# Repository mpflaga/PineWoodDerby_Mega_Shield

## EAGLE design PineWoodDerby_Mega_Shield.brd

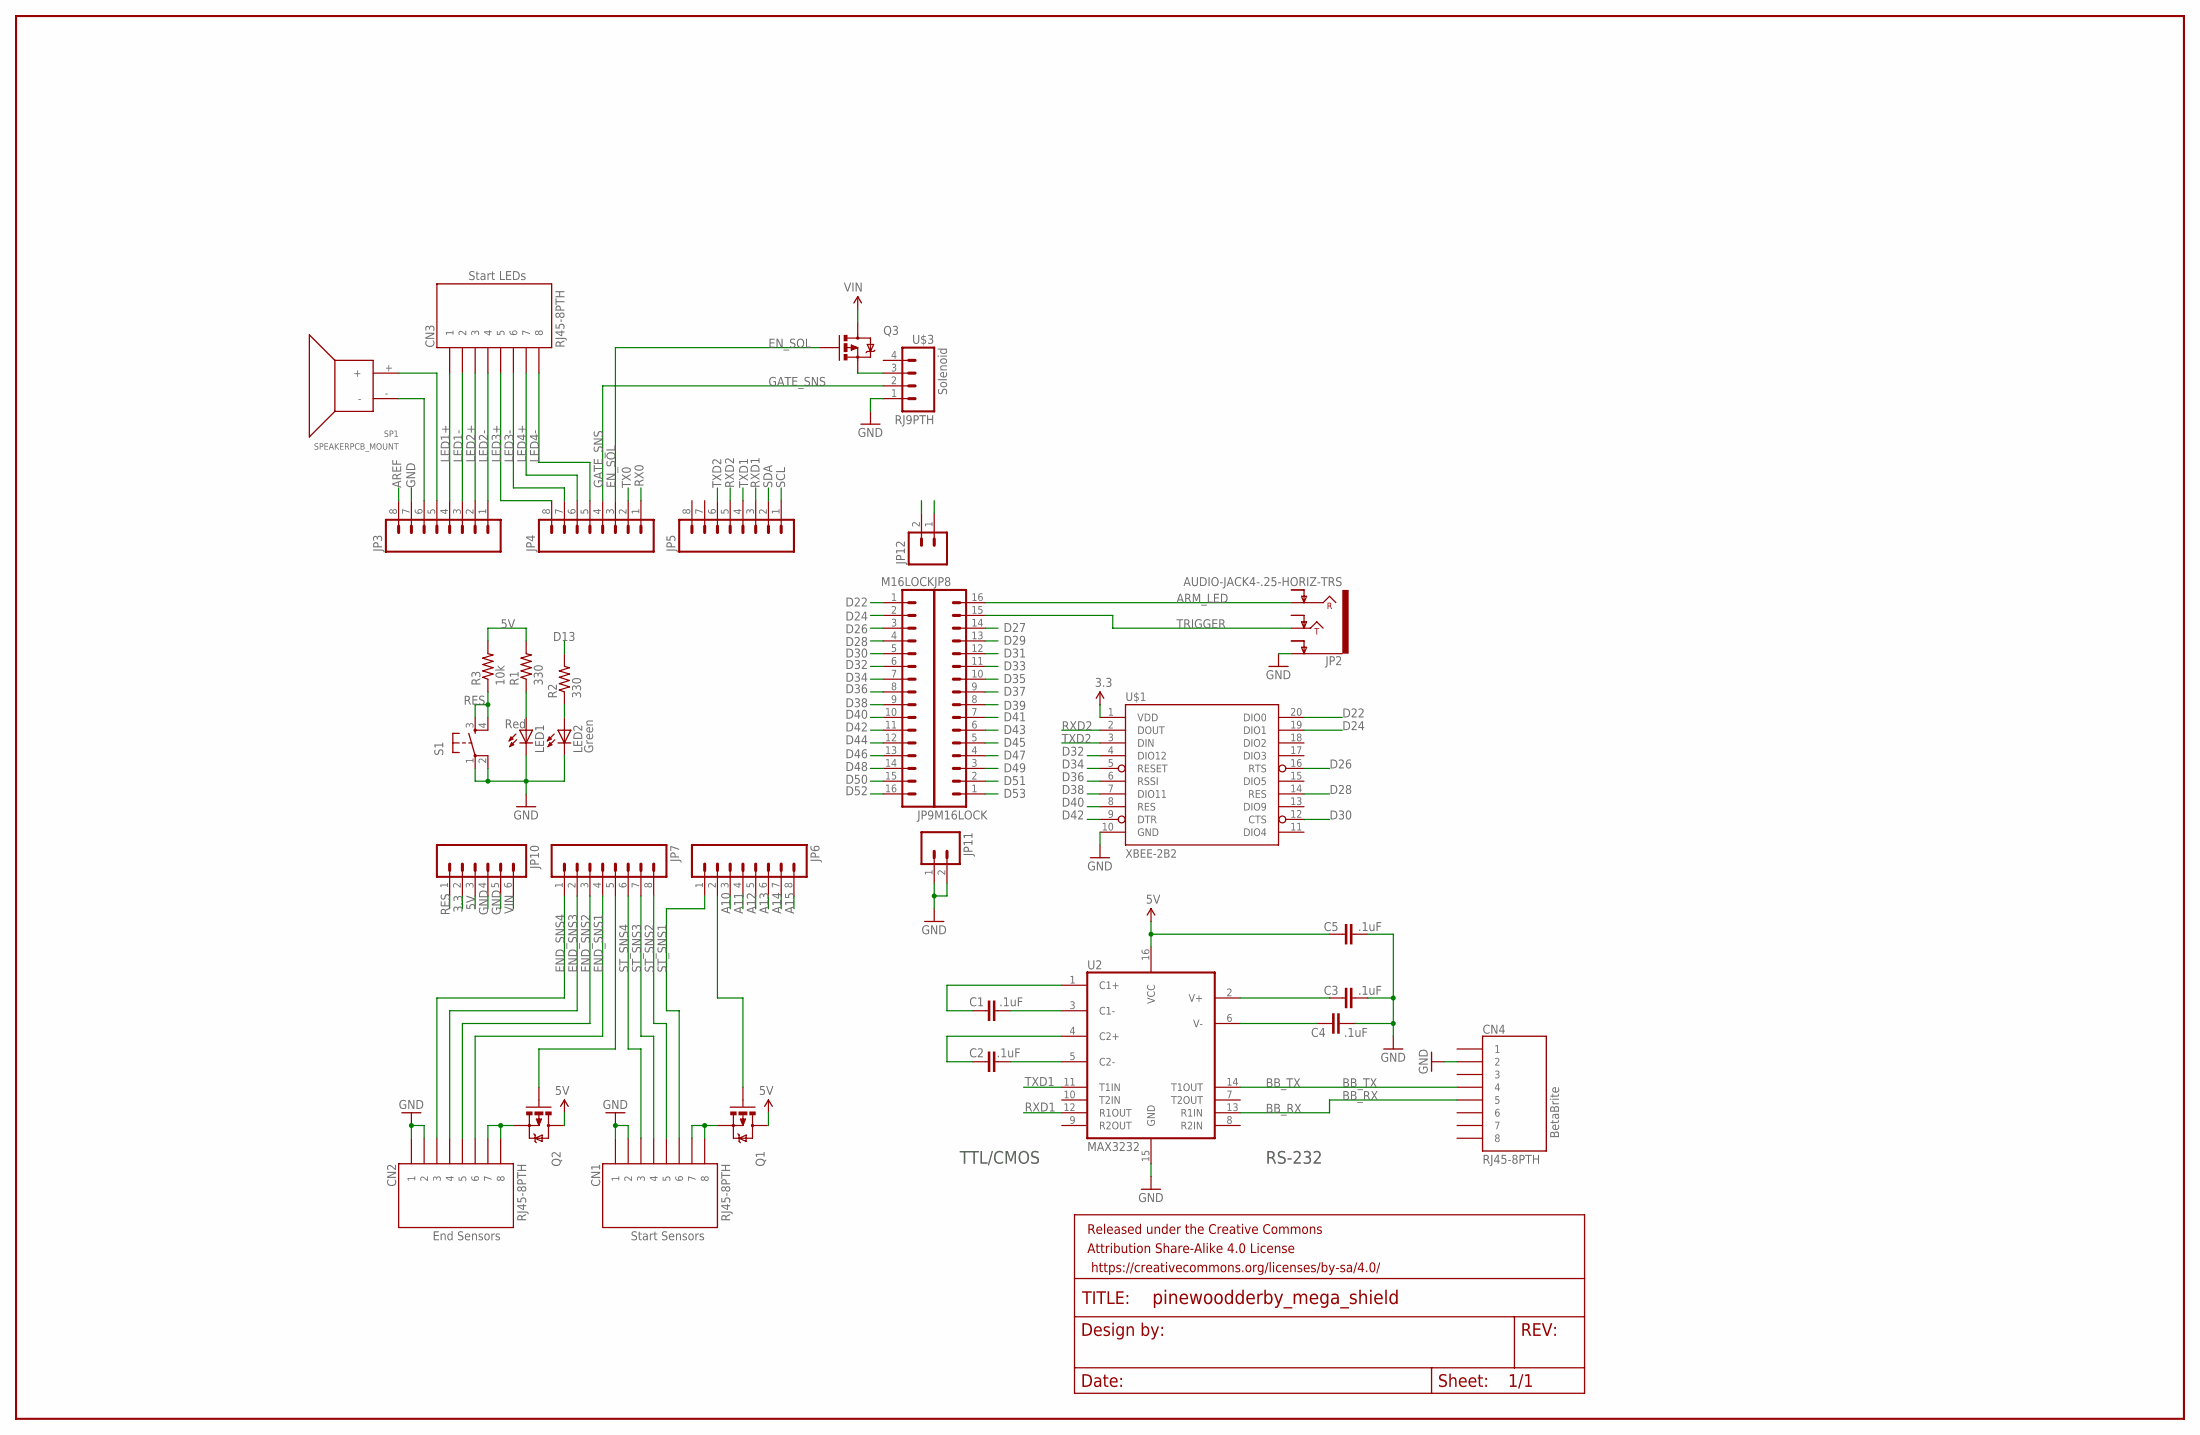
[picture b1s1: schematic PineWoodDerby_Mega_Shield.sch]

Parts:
C1, C2, C3, C4, C5: .1uF; 0402-CAP
CN1, CN2, CN3, CN4: RJ45-8PTH; RJ45-8
FRAME2: FRAME-LEDGER; CREATIVE_COMMONS
JP2: AUDIO-JACK4-.25-HORIZ-TRS; AUDIO-JACK-.25-INCH-HORIZ-PTH
JP3, JP4, JP5, JP6, JP7: M08LOCK; 1X08_LOCK
JP8, JP9: M16LOCK; 1X16_LOCK
JP10: M06LOCK; 1X06_LOCK
JP11, JP12: M02LOCK; 1X02_LOCK
LED1: Red; LED5MM
LED2: Green; LED5MM
Q1, Q2, Q3: MOSFET-PCHANNELFQP27P06; TO220V
R1, R2: 330; AXIAL-0.3
R3: 10k; AXIAL-0.3
S1: TAC_SWITCHPTH; TACTILE-PTH
SP1: SPEAKERPCB_MOUNT; PCB_MOUNT_SPEAKER
U2: MAX3232; SO016
U$1: XBEE-2B2; XBEE-SILK
U$3: RJ9PTH; RJ9

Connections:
3.3: JP10.2, U$1.1 (VDD)
5V: C5.1, JP10.3, Q1.2 (D), Q2.2 (D), R1.P$2 (2), R3.P$2 (2), U2.16 (VCC)
5V@1: JP12.1, JP12.2
A10: JP6.3
A11: JP6.4
A12: JP6.5
A13: JP6.6
A14: JP6.7
A15: JP6.8
AREF: JP3.8
ARM_LED: JP2.RING, JP8.16
BB_RX: CN4.5, U2.13 (R1IN)
BB_TX: CN4.4, U2.14 (T1OUT)
C1+: C1.1, U2.1 (C1+)
C1-: C1.2, U2.3 (C1-)
C2+: C2.1, U2.4 (C2+)
C2-: C2.2, U2.5 (C2-)
D13: R2.P$2 (2)
D22: JP9.1, U$1.20 (DIO0)
D24: JP9.2, U$1.19 (DIO1)
D26: JP9.3, U$1.16 (RTS)
D27: JP8.14
D28: JP9.4, U$1.14 (RES)
D29: JP8.13
D30: JP9.5, U$1.12 (CTS)
D31: JP8.12
D32: JP9.6, U$1.4 (DIO12)
D33: JP8.11
D34: JP9.7, U$1.5 (RESET)
D35: JP8.10
D36: JP9.8, U$1.6 (RSSI)
D37: JP8.9
D38: JP9.9, U$1.7 (DIO11)
D39: JP8.8
D40: JP9.10, U$1.8 (RES)
D41: JP8.7
D42: JP9.11, U$1.9 (DTR)
D43: JP8.6
D44: JP9.12
D45: JP8.5
D46: JP9.13
D47: JP8.4
D48: JP9.14
D49: JP8.3
D50: JP9.15
D51: JP8.2
D52: JP9.16
D53: JP8.1
END_SNS1: CN2.6, JP7.4
END_SNS2: CN2.5, JP7.3
END_SNS3: CN2.4, JP7.2
END_SNS4: CN2.3, JP7.1
EN_END_SNS: JP7.5, Q2.1 (G)
EN_SOL: JP4.3, Q3.1 (G)
EN_ST_SNS: JP6.2, Q1.1 (G)
GATE_SNS: JP4.4, U$3.2
GND: C3.2, C4.2, C5.2, CN1.1, CN1.2, CN2.1, CN2.2, CN4.2, JP2.SLEEVE (EARTH), JP3.7, JP10.4, JP10.5, JP11.1, JP11.2, LED1.K (C), LED2.K (C), S1.1, S1.2, U2.15 (GND), U$1.10 (GND), U$3.1
LED1+: CN3.1, JP3.4
LED1-: CN3.2, JP3.3
LED2+: CN3.3, JP3.2
LED2-: CN3.4, JP3.1
LED3+: CN3.5, JP4.8
LED3-: CN3.6, JP4.7
LED4+: CN3.7, JP4.6
LED4-: CN3.8, JP4.5
unnamed: JP3.5, SP1.+
unnamed: JP3.6, SP1.-
unnamed: CN2.7, CN2.8, Q2.3 (S)
unnamed: CN1.7, CN1.8, Q1.3 (S)
unnamed: Q3.3 (S), U$3.3
unnamed: LED1.A, R1.P$1 (1)
unnamed: LED2.A, R2.P$1 (1)
RES: JP10.1, R3.P$1 (1), S1.3, S1.4
RX0: JP4.1
RXD1: JP5.3, U2.12 (R1OUT)
RXD2: JP5.5, U$1.2 (DOUT)
SCL: JP5.1
SDA: JP5.2
ST_SNS1: CN1.6, JP6.1
ST_SNS2: CN1.5, JP7.8
ST_SNS3: CN1.4, JP7.7
ST_SNS4: CN1.3, JP7.6
TRIGGER: JP2.TIP, JP8.15
TX0: JP4.2
TXD1: JP5.4, U2.11 (T1IN)
TXD2: JP5.6, U$1.3 (DIN)
V+: C3.1, U2.2 (V+)
V-: C4.1, U2.6 (V-)
VIN: JP10.6, Q3.2 (D)

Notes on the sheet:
RS-232
TTL/CMOS

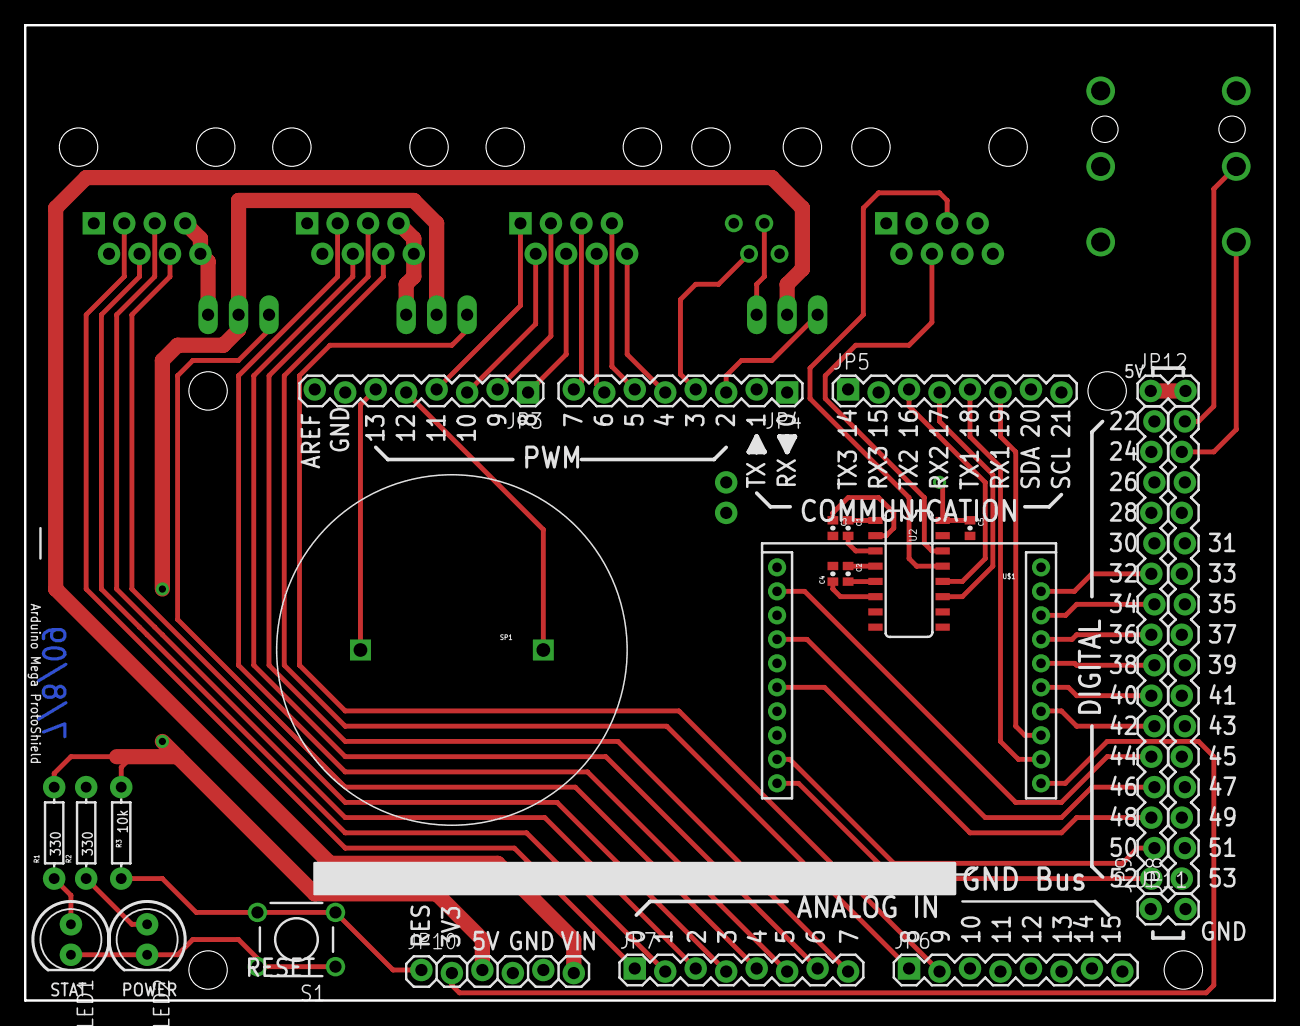
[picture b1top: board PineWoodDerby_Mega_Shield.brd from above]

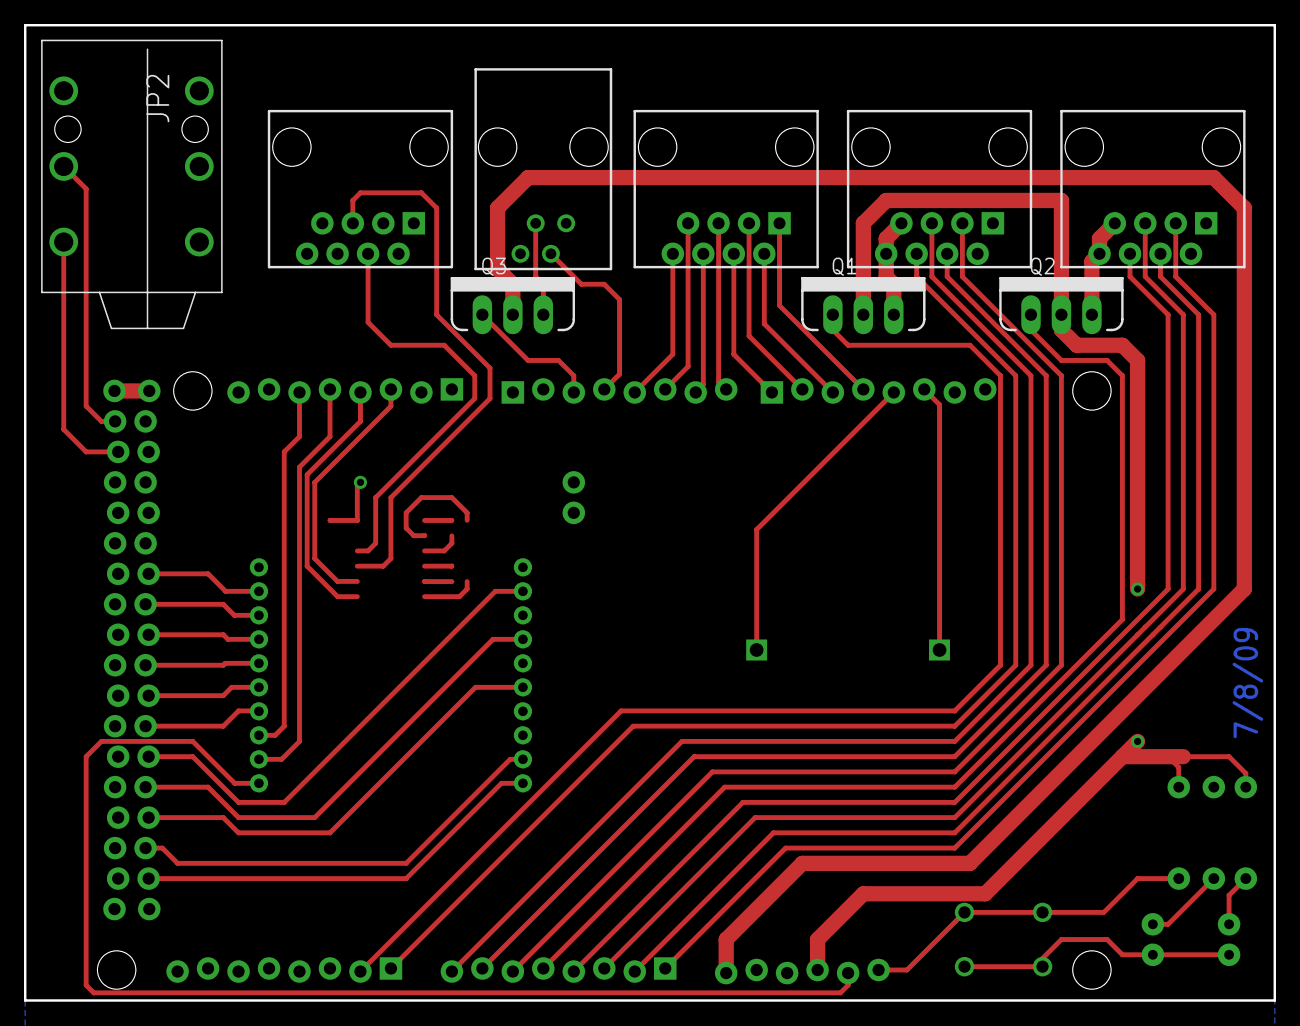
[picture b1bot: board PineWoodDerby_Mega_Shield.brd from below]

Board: 2 copper layers, 104.1 x 81.3 mm, 34 parts (9 on the bottom side), 58 nets.

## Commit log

2014-12-31 rename

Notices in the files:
parts and their libraries:
SparkFun-Connectors: Licensing: Creative Commons ShareAlike 4.0 International - https://creativecommons.org/licenses/by-sa/4.0
SparkFun-Passives: Licensing: CC v3.0 Share-Alike You are welcome to use this library for commercial purposes.
SparkFun-Aesthetics: Released under the Creative Commons
